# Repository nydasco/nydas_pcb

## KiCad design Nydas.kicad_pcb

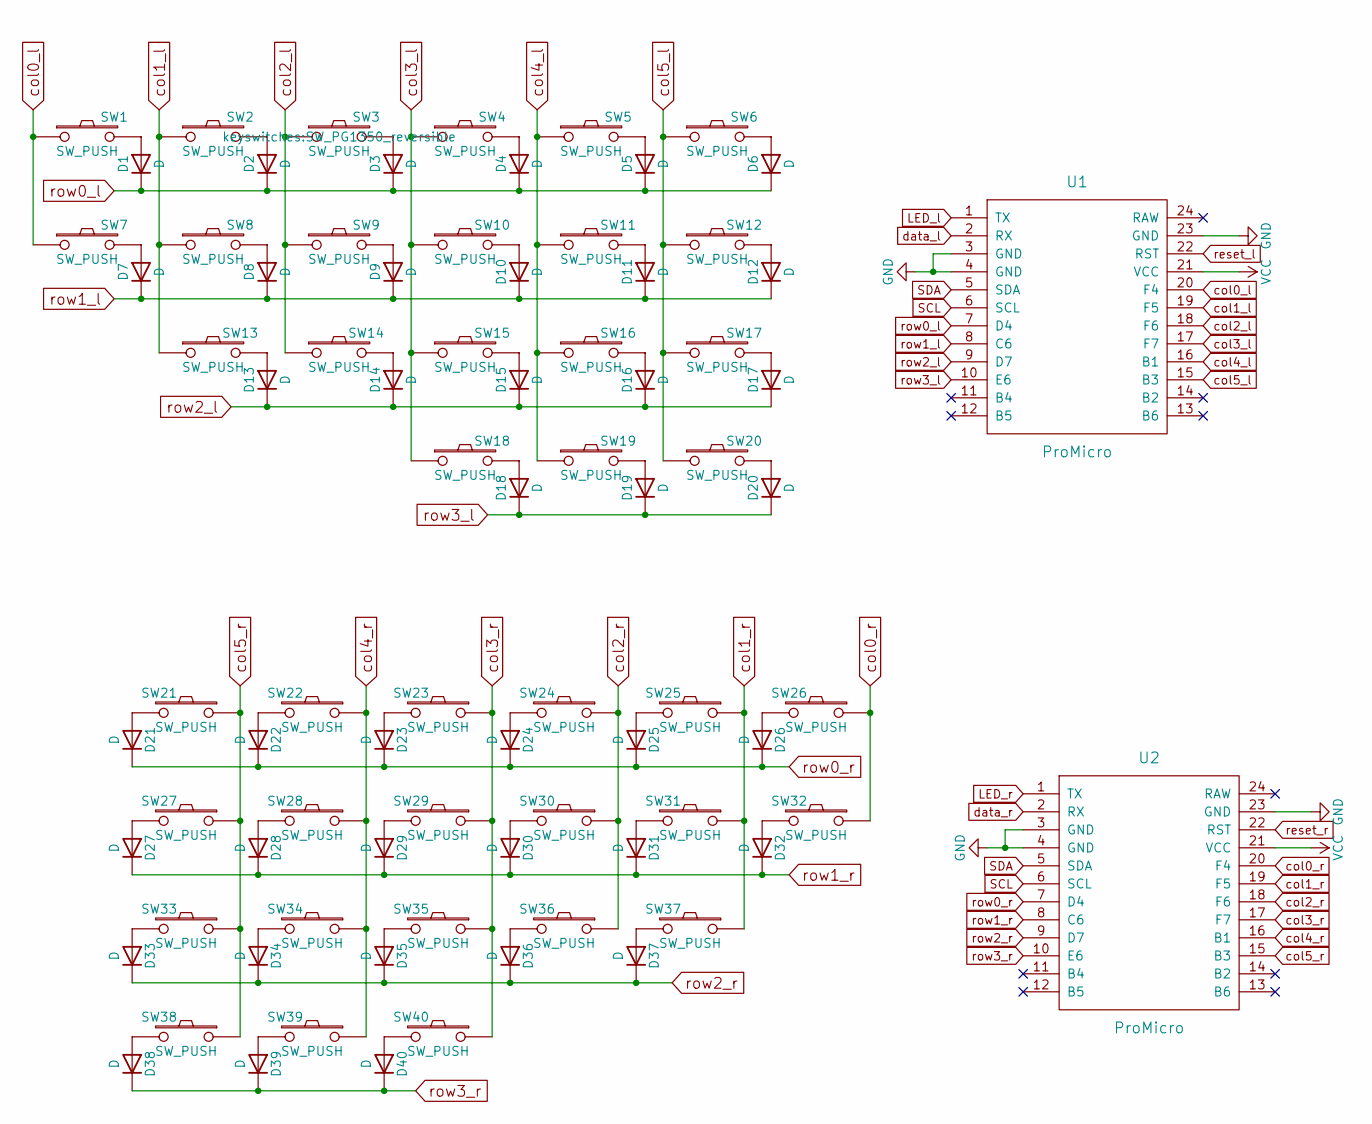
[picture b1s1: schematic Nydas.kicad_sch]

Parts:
D1, D2, D3, D4, D5, D6, D7, D8, D9, D10, D11, D12, D13, D14, D15, D16, D17, D18, D19, D20, D21, D22, D23, D24, D25, D26, D27, D28, D29, D30, D31, D32, D33, D34, D35, D36, D37, D38, D39, D40: D; D3_TH
SW1, SW2, SW3, SW4, SW5, SW6, SW7, SW8, SW9, SW10, SW11, SW12, SW13, SW14, SW15, SW16, SW17, SW18, SW19, SW20, SW21, SW22, SW23, SW24, SW25, SW26, SW27, SW28, SW29, SW30, SW31, SW32, SW33, SW34, SW35, SW36, SW37, SW38, SW39, SW40: SW_PUSH; SW_PG1350_reversible
U1, U2: ProMicro; SPARKFUN_PRO_MICRO

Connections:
GND: U1.3 (GND), U1.4 (GND), U1.23 (GND), U2.3 (GND), U2.4 (GND), U2.23 (GND)
LED_l: U1.1 (TX)
LED_r: U2.1 (TX)
unnamed: D1.2 (A), SW1.2
unnamed: D2.2 (A), SW2.2
unnamed: D3.2 (A), SW3.2
unnamed: D4.2 (A), SW4.2
unnamed: D5.2 (A), SW5.2
unnamed: D6.2 (A), SW6.2
unnamed: D7.2 (A), SW7.2
unnamed: D8.2 (A), SW8.2
unnamed: D9.2 (A), SW9.2
unnamed: D10.2 (A), SW10.2
unnamed: D11.2 (A), SW11.2
unnamed: D12.2 (A), SW12.2
unnamed: D13.2 (A), SW13.2
unnamed: D14.2 (A), SW14.2
unnamed: D15.2 (A), SW15.2
unnamed: D16.2 (A), SW16.2
unnamed: D17.2 (A), SW17.2
unnamed: D18.2 (A), SW18.2
unnamed: D19.2 (A), SW19.2
unnamed: D20.2 (A), SW20.2
unnamed: D21.2 (A), SW21.2
unnamed: D22.2 (A), SW22.2
unnamed: D23.2 (A), SW23.2
unnamed: D24.2 (A), SW24.2
unnamed: D25.2 (A), SW25.2
unnamed: D26.2 (A), SW26.2
unnamed: D27.2 (A), SW27.2
unnamed: D28.2 (A), SW28.2
unnamed: D29.2 (A), SW29.2
unnamed: D30.2 (A), SW30.2
unnamed: D31.2 (A), SW31.2
unnamed: D32.2 (A), SW32.2
unnamed: D33.2 (A), SW33.2
unnamed: D34.2 (A), SW34.2
unnamed: D35.2 (A), SW35.2
unnamed: D36.2 (A), SW36.2
unnamed: D37.2 (A), SW37.2
unnamed: D38.2 (A), SW38.2
unnamed: D39.2 (A), SW39.2
unnamed: D40.2 (A), SW40.2
SCL: U1.6 (SCL), U2.6 (SCL)
SDA: U1.5 (SDA), U2.5 (SDA)
VCC: U1.21 (VCC), U2.21 (VCC)
col0_l: SW1.1, SW7.1, U1.20 (F4)
col0_r: SW26.1, SW32.1, U2.20 (F4)
col1_l: SW2.1, SW8.1, SW13.1, U1.19 (F5)
col1_r: SW25.1, SW31.1, SW37.1, U2.19 (F5)
col2_l: SW3.1, SW9.1, SW14.1, U1.18 (F6)
col2_r: SW24.1, SW30.1, SW36.1, U2.18 (F6)
col3_l: SW4.1, SW10.1, SW15.1, SW18.1, U1.17 (F7)
col3_r: SW23.1, SW29.1, SW35.1, SW40.1, U2.17 (F7)
col4_l: SW5.1, SW11.1, SW16.1, SW19.1, U1.16 (B1)
col4_r: SW22.1, SW28.1, SW34.1, SW39.1, U2.16 (B1)
col5_l: SW6.1, SW12.1, SW17.1, SW20.1, U1.15 (B3)
col5_r: SW21.1, SW27.1, SW33.1, SW38.1, U2.15 (B3)
data_l: U1.2 (RX)
data_r: U2.2 (RX)
reset_l: U1.22 (RST)
reset_r: U2.22 (RST)
row0_l: D1.1 (K), D2.1 (K), D3.1 (K), D4.1 (K), D5.1 (K), D6.1 (K), U1.7 (D4)
row0_r: D21.1 (K), D22.1 (K), D23.1 (K), D24.1 (K), D25.1 (K), D26.1 (K), U2.7 (D4)
row1_l: D7.1 (K), D8.1 (K), D9.1 (K), D10.1 (K), D11.1 (K), D12.1 (K), U1.8 (C6)
row1_r: D27.1 (K), D28.1 (K), D29.1 (K), D30.1 (K), D31.1 (K), D32.1 (K), U2.8 (C6)
row2_l: D13.1 (K), D14.1 (K), D15.1 (K), D16.1 (K), D17.1 (K), U1.9 (D7)
row2_r: D33.1 (K), D34.1 (K), D35.1 (K), D36.1 (K), D37.1 (K), U2.9 (D7)
row3_l: D18.1 (K), D19.1 (K), D20.1 (K), U1.10 (E6)
row3_r: D38.1 (K), D39.1 (K), D40.1 (K), U2.10 (E6)

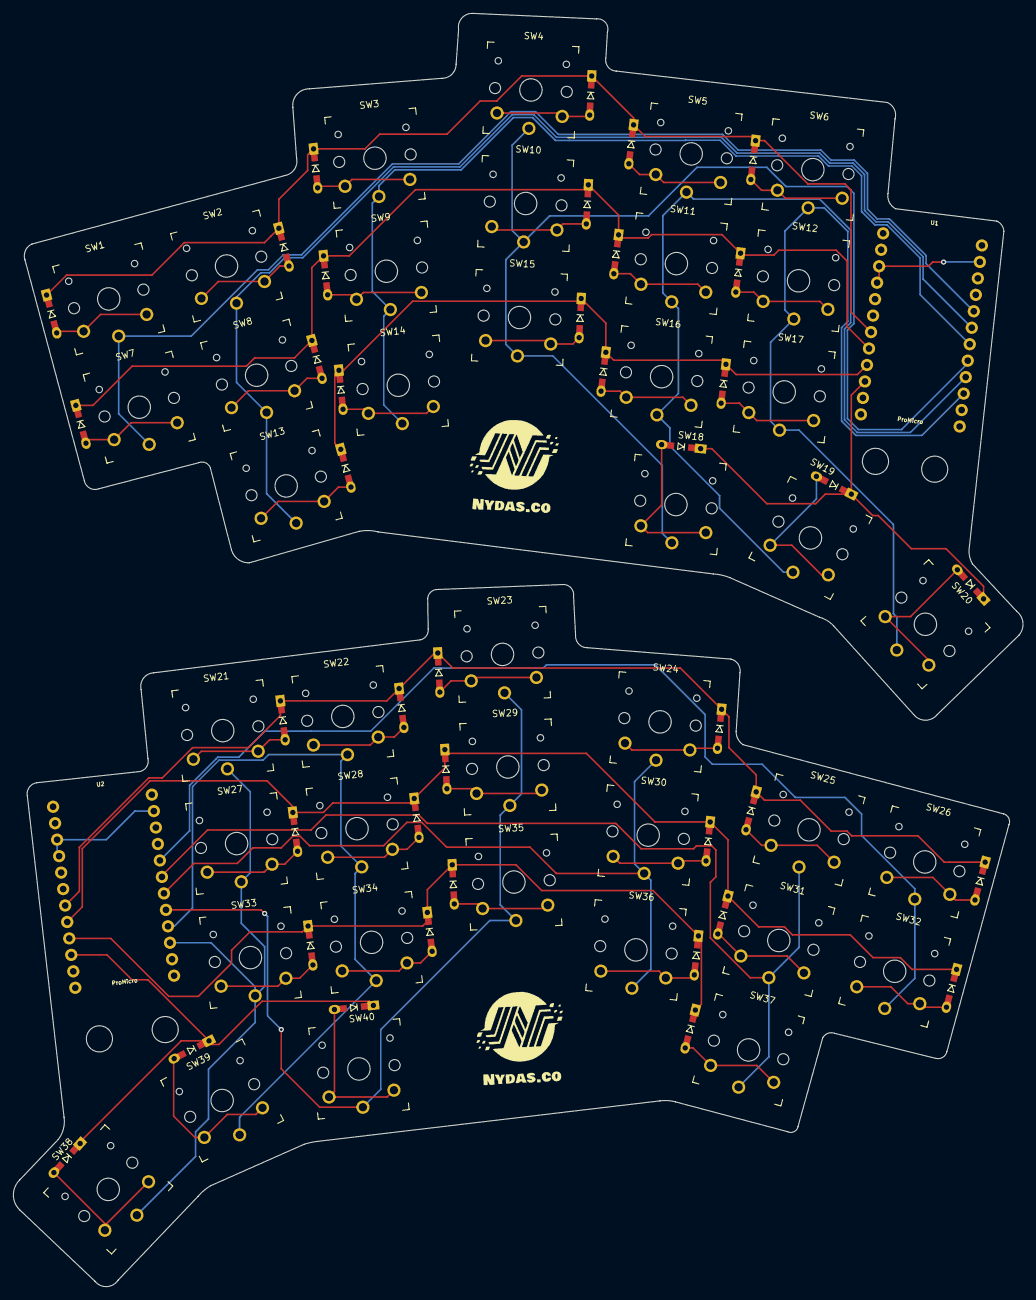
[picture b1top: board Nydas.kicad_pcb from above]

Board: 2 copper layers, 154.7 x 195.0 mm, 84 parts (0 on the bottom side), 64 nets.

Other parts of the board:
G1, G1#2: LOGO; nydas_kicad

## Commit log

2022-04-08 init
